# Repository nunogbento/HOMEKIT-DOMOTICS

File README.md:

# HOMEKIT-DOMOTICS

Personal collection of home-automation hardware and firmware around Apple HomeKit,
spanning multiple generations of boards and HomeKit integration techniques.

## Project layout

Each top-level folder is one project. Projects with a custom PCB have:

```
<Project>/
├── firmware/      one subfolder per firmware version (generation)
├── circuit/       PCB design files (.brd / .sch / .cam)
└── enclosure/     3D-printable bodies (where applicable)
```

Projects without a custom PCB omit `circuit/`, and use `enclosure/` only if a
3D-printed body exists.

## Active projects

### [PCCWDplus](PCCWDplus/) — custom PCB
Main panel board. Succession: MQTT (ESP8266) → HomeSpan (ESP32-C5).
Gen 2 (HAP/ESP8266) was attempted but failed; see archive notes.
- `firmware/Mqtt.MordomusESP8266/` — gen 1, MQTT/ESP8266 — **deployed**
- `firmware/HSPCCWDplus/` — gen 3, HomeSpan/ESP32-C5 — **WIP**, pin-compatible drop-in

### [MultiAccessory](MultiAccessory/) — custom PCB
Multi-device controller board. Gen 2 still deployed, gen 3 in progress.
- `firmware/HKMultiAccessory/` — gen 2, HAP/ESP8266 — **deployed**
- `firmware/HSPMultiAccessory/` — gen 3, HomeSpan/ESP32-C5 — **WIP**
- `firmware/HKSprinklerValve/` — gen 2 valve variant on the same board

### [ESP8266-ADC](ESP8266-ADC/) — custom PCB
Shared ESP8266-with-ADC board used for analog sensing applications.
- `firmware/HKSolarPanel/` — gen 2, HAP/ESP8266 — **deployed**, no successor planned
- `firmware/mqtt-SolarPanel/` — gen 1, archived firmware
- `firmware/Mqtt.ESP8266PlantComputer/` — gen 1, archived firmware

### [HSPCCWD](HSPCCWD/) — no custom hardware
HomeSpan reference implementation on a bare ESP32 devkit, serial-only.

### [ESP32Door](ESP32Door/) — no custom hardware
Door sensor using an off-the-shelf ESP32 module + 3D-printed enclosure.

### [Feeder](Feeder/) — no custom hardware, 3D-printed body
- `firmware/HKFEEDER/` — current
- `firmware/mqtt-RabitFeeder/` — earlier version

## HomeKit firmware generations

| Gen | Stack           | Chip         | Status                                |
|-----|-----------------|--------------|---------------------------------------|
| 1   | MQTT bridge     | ESP8266      | Mqtt.MordomusESP8266 still deployed   |
| 2   | Arduino-HomeKit | ESP8266      | HKMultiAccessory, HKSolarPanel still deployed; HKPCCWD archived (failed) |
| 3   | HomeSpan        | ESP32 / C5   | HSPCCWDplus, HSPMultiAccessory — WIP  |

Gen 2 failed on the PCCWD board because the ESP8266 could not handle HomeKit
at that board's accessory complexity. That's why the PCCWD lineage jumps
directly from gen 1 (MQTT) to gen 3 (HomeSpan).

## archive/

Everything superseded, retired, unfinished, unrelated, or not tied to an
active hardware project. Includes:
- `HKPCCWD/` (gen 2 failure)
- Early MQTT experiments (lightbulbs, rollerblinds, power meter, etc.)
- Side experiments (CameraWebServer, ESP-32CAM, SONOFFAPI, WaterDetector)
- `Tradfri-ICC-1/` — reverse-engineering research that informed MultiAccessory
- `MordomusAPI/`, `PowerMeter/`, `pccwdapi/`, `node-red-contrib-pccwd/` — no longer used
- `homebridge-host/` — Homebridge configuration, Node-RED flows, backups

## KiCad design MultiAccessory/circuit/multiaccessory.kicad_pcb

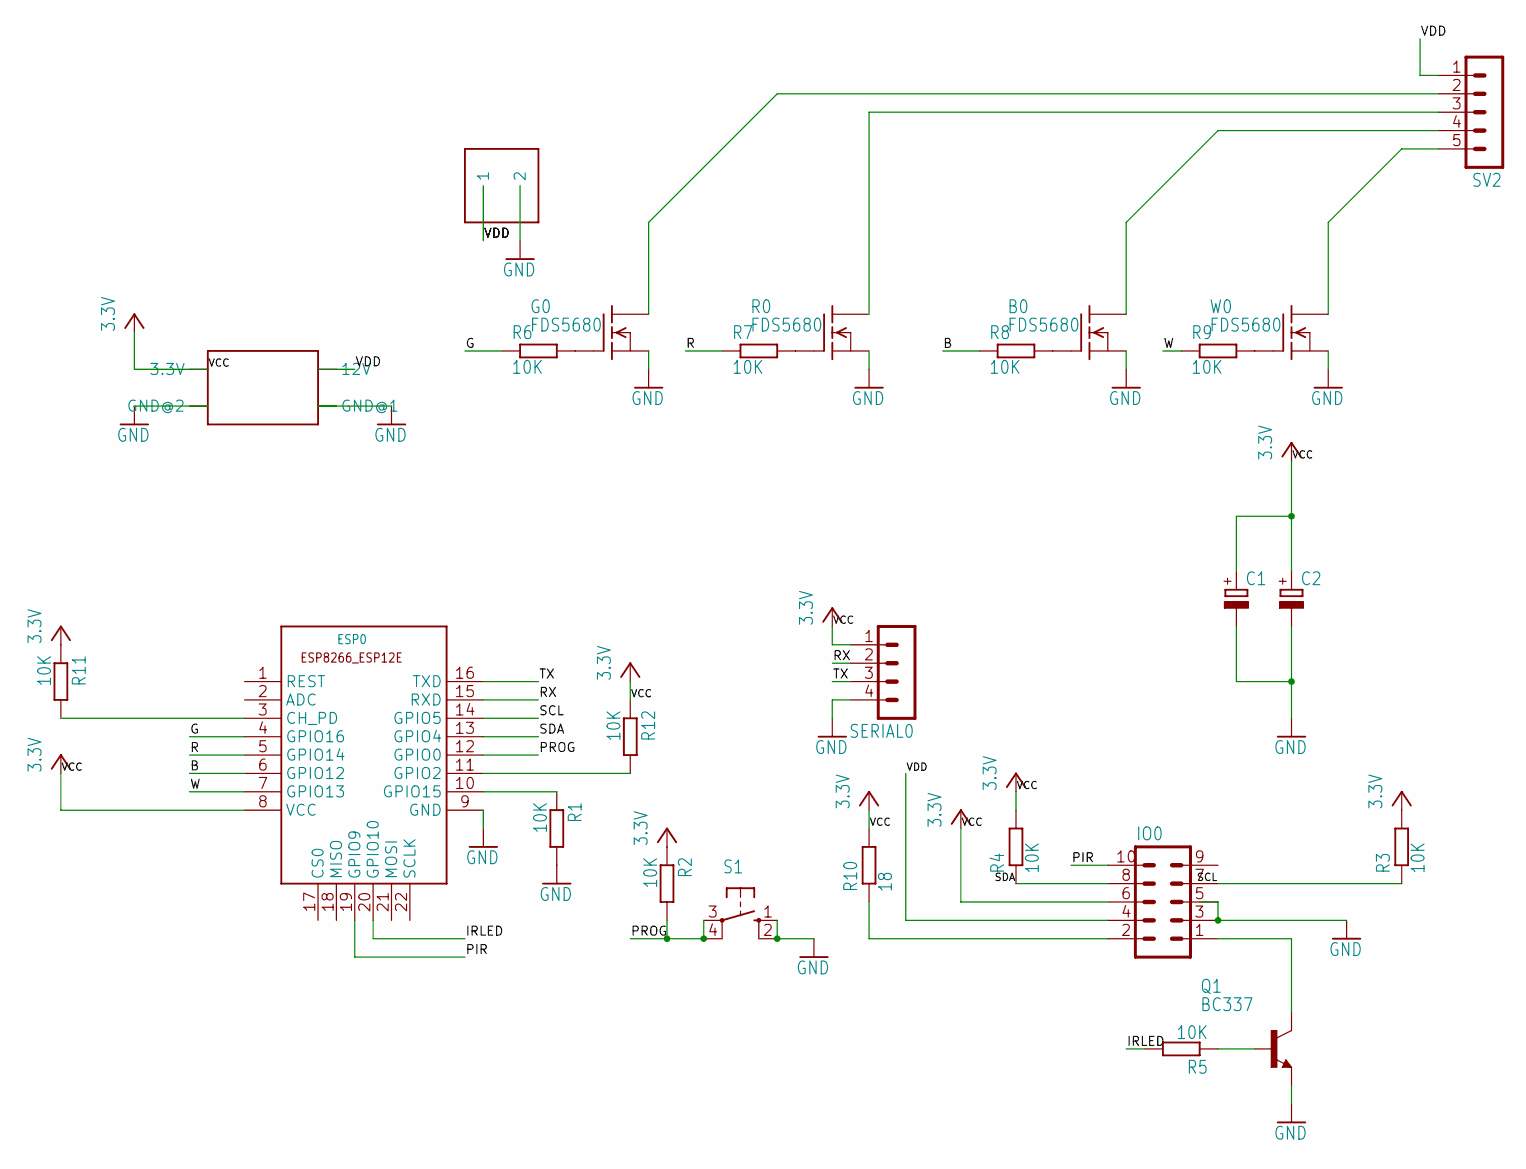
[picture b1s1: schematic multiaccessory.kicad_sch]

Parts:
B0: FDS5680; SO-8
C1, C2: CPOL-EUE2-5; E2-5
ESP0: ESP8266-12EESP8266-ESP12E; ESP8266-ESP12E
G0: FDS5680; SO-8
IO0: MA05-2
PWR1: MP2307-MINI-360
PWR_IN0: KF350-P2; KF350-2P
Q1: BC337; TO92
R0: FDS5680; SO-8
R1, R2, R3, R4, R5, R6, R7, R8, R9, R11, R12: 10K; R0603
R10: 18; R0603
S1: 10-XX; B3F-10XX
SERIAL0: MA04-1
SV2: MA05-1
W0: FDS5680; SO-8

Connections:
B: ESP0.6 (GPIO12), R8.1
DB: B0.5 (D), B0.6 (D), B0.7 (D), B0.8 (D), SV2.4
DG: G0.5 (D), G0.6 (D), G0.7 (D), G0.8 (D), SV2.2
DR: R0.5 (D), R0.6 (D), R0.7 (D), R0.8 (D), SV2.3
DW: SV2.5, W0.5 (D), W0.6 (D), W0.7 (D), W0.8 (D)
G: ESP0.4 (GPIO16), R6.1
GND: B0.1 (S), B0.2 (S), B0.3 (S), C1.-, C2.-, ESP0.9 (GND), G0.1 (S), G0.2 (S), G0.3 (S), IO0.3, IO0.5, PWR1.GND@1, PWR1.GND@2, PWR_IN0.2, Q1.1 (E), R0.1 (S), R0.2 (S), R0.3 (S), R1.2, S1.1 (S), S1.2 (S1), SERIAL0.4, W0.1 (S), W0.2 (S), W0.3 (S)
IRLED: ESP0.20 (GPIO10), R5.2
unnamed: ESP0.10 (GPIO15), R1.1
unnamed: ESP0.3 (CH_PD), R11.2
unnamed: ESP0.11 (GPIO2), R12.2
unnamed: G0.4 (G), R6.2
unnamed: Q1.2 (B), R5.1
unnamed: R0.4 (G), R7.2
unnamed: B0.4 (G), R8.2
unnamed: R9.2, W0.4 (G)
unnamed: IO0.2, R10.1
unnamed: IO0.1, Q1.3 (C)
PIR: ESP0.19 (GPIO9), IO0.10
PROG: ESP0.12 (GPIO0), R2.2, S1.3, S1.4 (P1)
R: ESP0.5 (GPIO14), R7.1
RX: ESP0.15 (RXD), SERIAL0.2
SCL: ESP0.14 (GPIO5), IO0.7, R3.1
SDA: ESP0.13 (GPIO4), IO0.8, R4.1
TX: ESP0.16 (TXD), SERIAL0.3
VCC: C1.+, C2.+, ESP0.8 (VCC), IO0.6, PWR1.3.3V, R2.1, R3.2, R4.2, R10.2, R11.1, R12.1, SERIAL0.1
VDD: IO0.4, PWR1.12V, PWR_IN0.1, SV2.1
W: ESP0.7 (GPIO13), R9.1

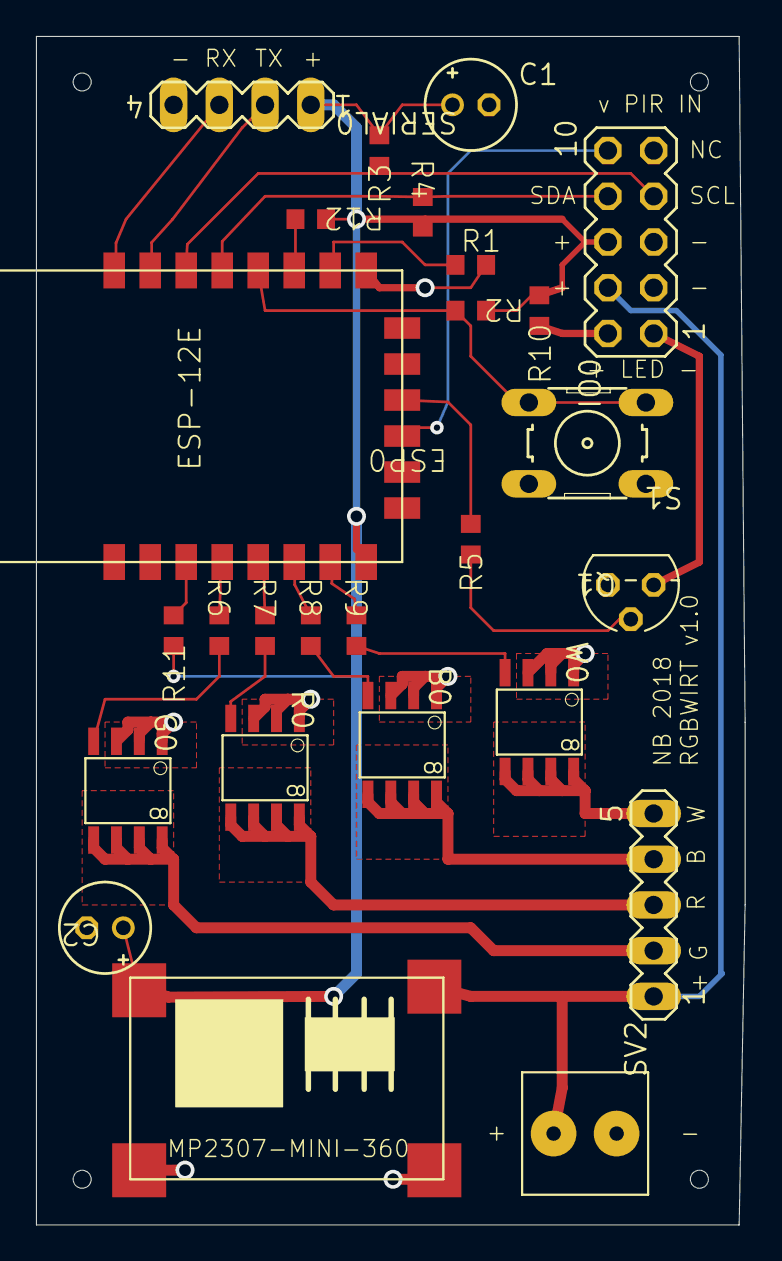
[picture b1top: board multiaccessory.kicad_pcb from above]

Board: 2 copper layers, 39.4 x 66.0 mm, 30 parts (0 on the bottom side), 28 nets.

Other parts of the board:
UNK_HOLE_0: dummyfp0
UNK_HOLE_1: dummyfp1
UNK_HOLE_2: dummyfp2
UNK_HOLE_3: dummyfp3

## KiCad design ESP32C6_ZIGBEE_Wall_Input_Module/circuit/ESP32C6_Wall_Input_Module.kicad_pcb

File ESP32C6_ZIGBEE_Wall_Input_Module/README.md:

# ESP32-C6 Zigbee In-Wall Input Module

A mains-powered, DIY alternative to the Philips Hue in-wall switch module.

It sits in the wall box behind your existing light switch, keeps the smart
bulbs **permanently powered**, and re-purposes the old mechanical switch as
two low-voltage inputs exposed over Zigbee. Because it runs off mains (not a
coin cell), it joins the mesh as a **Zigbee router**, strengthening the
network instead of being one more sleepy battery device.

## How it works

- A Hi-Link **HLK-PM01** (230 VAC → 5 V) feeds an **AMS1117-3.3**, powering a
  **WT0132C6-S5** (ESP32-C6 in the hand-solderable ESP-12F form factor).
- The lamp's live wire is bridged permanently on (joined with a Wago in the
  box) — the module never switches the load.
- The two existing switch contacts wire to two GPIO inputs (10 kΩ pull-up +
  RC filter each) and are published to Zigbee2MQTT as a **scene switch** —
  button *actions* (single / double / long, plus toggle/on/off), the same
  model as a Hue dimmer or a Modomus switch. HomeKit sees a **Stateless
  Programmable Switch**, not a door sensor.
- Each input's behaviour is **configurable from the Z2M profile** (see
  *Firmware behaviour* below), so the module works with a momentary push
  button *or* a bi-stable (rocker) toggle switch.

> ⚠️ **230 VAC.** Primary side is fused + MOV-protected and separated from the
> low-voltage side by a milled creepage slot (≥6 mm). The switch wires become
> SELV — disconnect them from mains before landing them. Needs a Neutral in
> the box (or install at the ceiling rose). See [HARDWARE.md](HARDWARE.md).

## Firmware behaviour

Each channel is a `genMultistateInput` endpoint reporting an **action**; a
`genMultistateOutput` on the same endpoint holds that channel's **mode**,
writable live from the Z2M UI and persisted in NVS.

| `mode_1` / `mode_2` | Emits | For |
|---|---|---|
| `momentary` *(default)* | `single` / `double` / `hold` | push buttons |
| `toggle` | `toggle` on every flip | rocker → HA does `light.toggle` |
| `toggle_directional` | `on` (closed) / `off` (open) | sync lamp to switch position |
| `toggle_scenes` | `single` / `double` from flip-count | multi-flip scenes off a rocker |

Actions arrive as `button_{1,2}_{single,double,hold,toggle,on,off}`.

**Diagnostics** (Z2M, diagnostic category):
- `device_temperature` — MCU die temp (health/overheat trend, not accurate
  ambient). **Polled** by the converter (a read every ~5 min), not reported:
  every Zigbee attribute-*report* path crashes this ESP-Zigbee build, so the
  firmware only refreshes the value and Z2M reads it. See the sketch header.
- `brownout_count` — increments on a brownout/unexpected reset, so a unit
  browning out in a wall reveals itself remotely with no serial cable.

**Zigbee OTA** — the module carries an OTA client, so after the first (wired)
flash every future update is wireless via Z2M's OTA override index, and images
are **rollback-guarded** (a bad boot reverts automatically). See
[ota/README.md](ota/README.md) for the full build → deploy → update process.

## Status

| Item | State |
|---|---|
| Schematic | ✅ Complete, ERC-clean (KiCad 10); WT0132C6-S5 symbol pinout corrected |
| PCB layout | ✅ Routed, DRC-clean — 45 × 36 mm, 2-layer (status LED on IO7 / pin 10) |
| Firmware | ✅ v8 (`0x01000007`) — scene-switch actions, per-channel modes, rollback-guarded OTA, polled temp + brownout telemetry |
| Z2M converter | ✅ External converter (actions + mode enums + diagnostics; temp polled) |
| Fabrication | 📦 Gerbers exported; **both boards hand-built, on mains, on v8, validated (buttons + modes + temp + brownout), ready to install** |
| OTA proven | ✅ Board 1 updated in-wall v3→v8 over the mesh (rollback-guarded) |

> **Regulator note:** use a *genuine* AMS1117-3.3. A counterfeit part that
> can't source the radio-TX surge causes brownouts on join (cool reg, low LQI,
> won't stay paired). Confirmed by bench-3.3 V bypass; fixed by a real part.
> See [HARDWARE.md](HARDWARE.md).

## Repository contents

| Path | What |
|---|---|
| [`ESP32C6_ZIGBEE_Wall_Input_Module.ino`](ESP32C6_ZIGBEE_Wall_Input_Module.ino) | Arduino sketch (compile-time board switch: WT0132C6-S5 or XIAO ESP32C6 prototype) |
| [`HARDWARE.md`](HARDWARE.md) | Circuit design, net-by-net description, BOM, install guide |
| [`ASSEMBLY.md`](ASSEMBLY.md) | Hand-assembly guide: part IDs/markings, build order, staged bring-up tests |
| [`FABRICATION.md`](FABRICATION.md) | JLCPCB order settings + gerber package |
| [`diy_esp32c6_2ch_input.js`](diy_esp32c6_2ch_input.js) | Zigbee2MQTT external converter (actions, per-channel mode enums, temp + brownout diagnostics, OTA) |
| [`ota/`](ota/) | Zigbee OTA: `make_ota.py` image builder, current `index.json` + `.ota` (mirrors the Pi's `ota_override/`), and [`ota/README.md`](ota/README.md) — the full update process |
| [`circuit/`](circuit/) | KiCad 10 project — schematic, board, custom WT0132C6-S5 library, gerbers (`fab/`) |
| [`docs/`](docs/) | Rendered board + schematic images |

## Board

| Top (mains side) | Bottom (logic side) |
|---|---|
|  |  |

The HLK-PM01 and screw terminals are on top; the WT0132C6-S5 is on the bottom
with its antenna overhanging the board edge. The notch in the ground pour and
the milled slot keep the 230 V primary isolated from the SELV side.

## Prototype / bring-up bench

The bring-up rig: WT0132C6-S5 board (blue status LED lit) fed from the
HLK-PM01, a USB-UART for the first flash, test-clip leads to the two inputs,
and a real dual **rocker** wall switch on the bench — the setup used to
validate the toggle-switch modes and the genuine-AMS1117 fix.

## Firmware build

Arduino IDE with the ESP32 core (Zigbee ZCZR mode + partition). Pick the board
at the top of the sketch:

```c
//#define BOARD_XIAO_ESP32C6    // breadboard prototype
#define BOARD_WT0132C6_S5       // final mains board
```

First flash is over UART (hold IO9 low, pulse EN); **after that, update over
the air** via Z2M OTA — no wires. Hold the BOOT button 5 s to factory reset /
re-pair. Status LED (IO7, active-low) blinks while joining, solid ~3 s when
connected, then off (it lives in a wall).

## Schematic

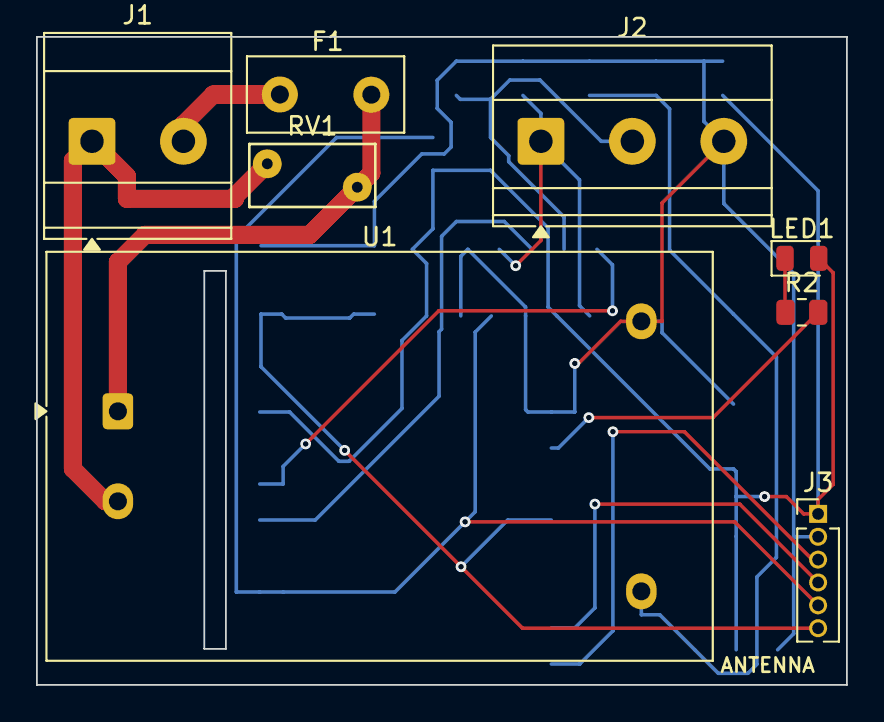
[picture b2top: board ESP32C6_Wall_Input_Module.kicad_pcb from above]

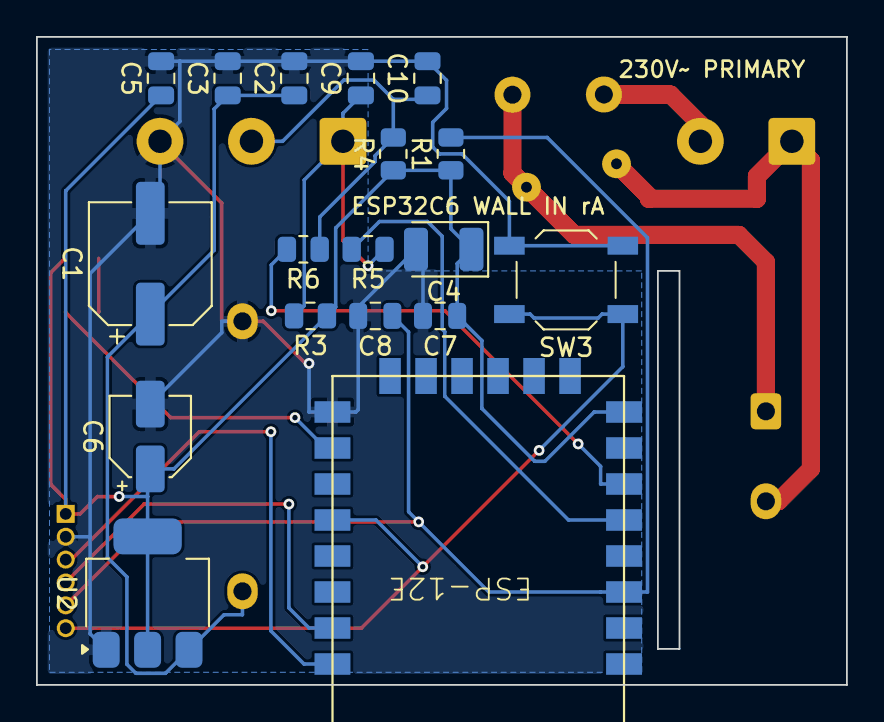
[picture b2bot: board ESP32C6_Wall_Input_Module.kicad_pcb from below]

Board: 2 copper layers, 45.0 x 36.0 mm, 26 parts (18 on the bottom side), 16 nets.

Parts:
C1: 100u; CP_Elec_6.3x5.4
C2, C5, C7, C9, C10: 100n; C_0805_2012Metric
C3: 10u; C_0805_2012Metric
C4: 22u; CP_EIA-3528-21_Kemet-B
C6: 47u; CP_Elec_4x5.4
C8: 1u; C_0805_2012Metric
F1: 500mA T; Fuse_Littelfuse_395Series
J1: MAINS IN; TerminalBlock_Phoenix_MKDS-3-2-5.08_1x02_P5.08mm_Horizontal
J2: WALL SWITCHES; TerminalBlock_Phoenix_MKDS-1,5-3-5.08_1x03_P5.08mm_Horizont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
J3: PROG; PinHeader_1x06_P1.27mm_Vertical
LED1: STATUS; LED_0805_2012Metric
R1, R3, R4: 10k; R_0805_2012Metric
R2, R5, R6: 1k; R_0805_2012Metric
RV1: 275VAC; RV_Disc_D7mm_W3.5mm_P5mm
SW3: BOOT; SW_SPST_TL3342
U1: HLK-PM01; Converter_ACDC_Hi-Link_HLK-PMxx
U2: AMS1117-3.3; SOT-223-3_TabPin2
U3: WT0132C6-S5

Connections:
+3V3: C4.1, C5.1, C6.1, C7.1, J3.1, LED1.2 (A), R1.1, R3.1, R4.1, U2.2 (VO), U3.8 (VCC)
+5V: C1.1, C2.1, C3.1, U1.4 (+Vout), U2.3 (VI)
/EN: C8.1, J3.5, R1.2, U3.3 (EN)
/IO9: J3.6, SW3.1, U3.12 (IO9)
/L: F1.1, J1.2
/N: J1.1, RV1.2, U1.2 (AC/N)
/RXD0: J3.4, U3.15 (RXD)
/STATUS_LED: R2.2, U3.10 (IO7)
/SW1: C9.1, J2.1, R3.2, R5.1
/SW1_IN: R5.2, U3.5 (IO4/MTMS)
/SW2: C10.1, J2.2, R4.2, R6.1
/SW2_IN: R6.2, U3.6 (IO5/MTDI)
/TXD0: J3.3, U3.16 (TXD)
GND: C1.2, C2.2, C3.2, C4.2, C5.2, C6.2, C7.2, C8.2, C9.2, C10.2, J2.3, J3.2, SW3.2, U1.3 (-Vout), U2.1 (GND), U3.9 (GND)
unnamed: LED1.1 (K), R2.1
unnamed: F1.2, RV1.1, U1.1 (AC/L)

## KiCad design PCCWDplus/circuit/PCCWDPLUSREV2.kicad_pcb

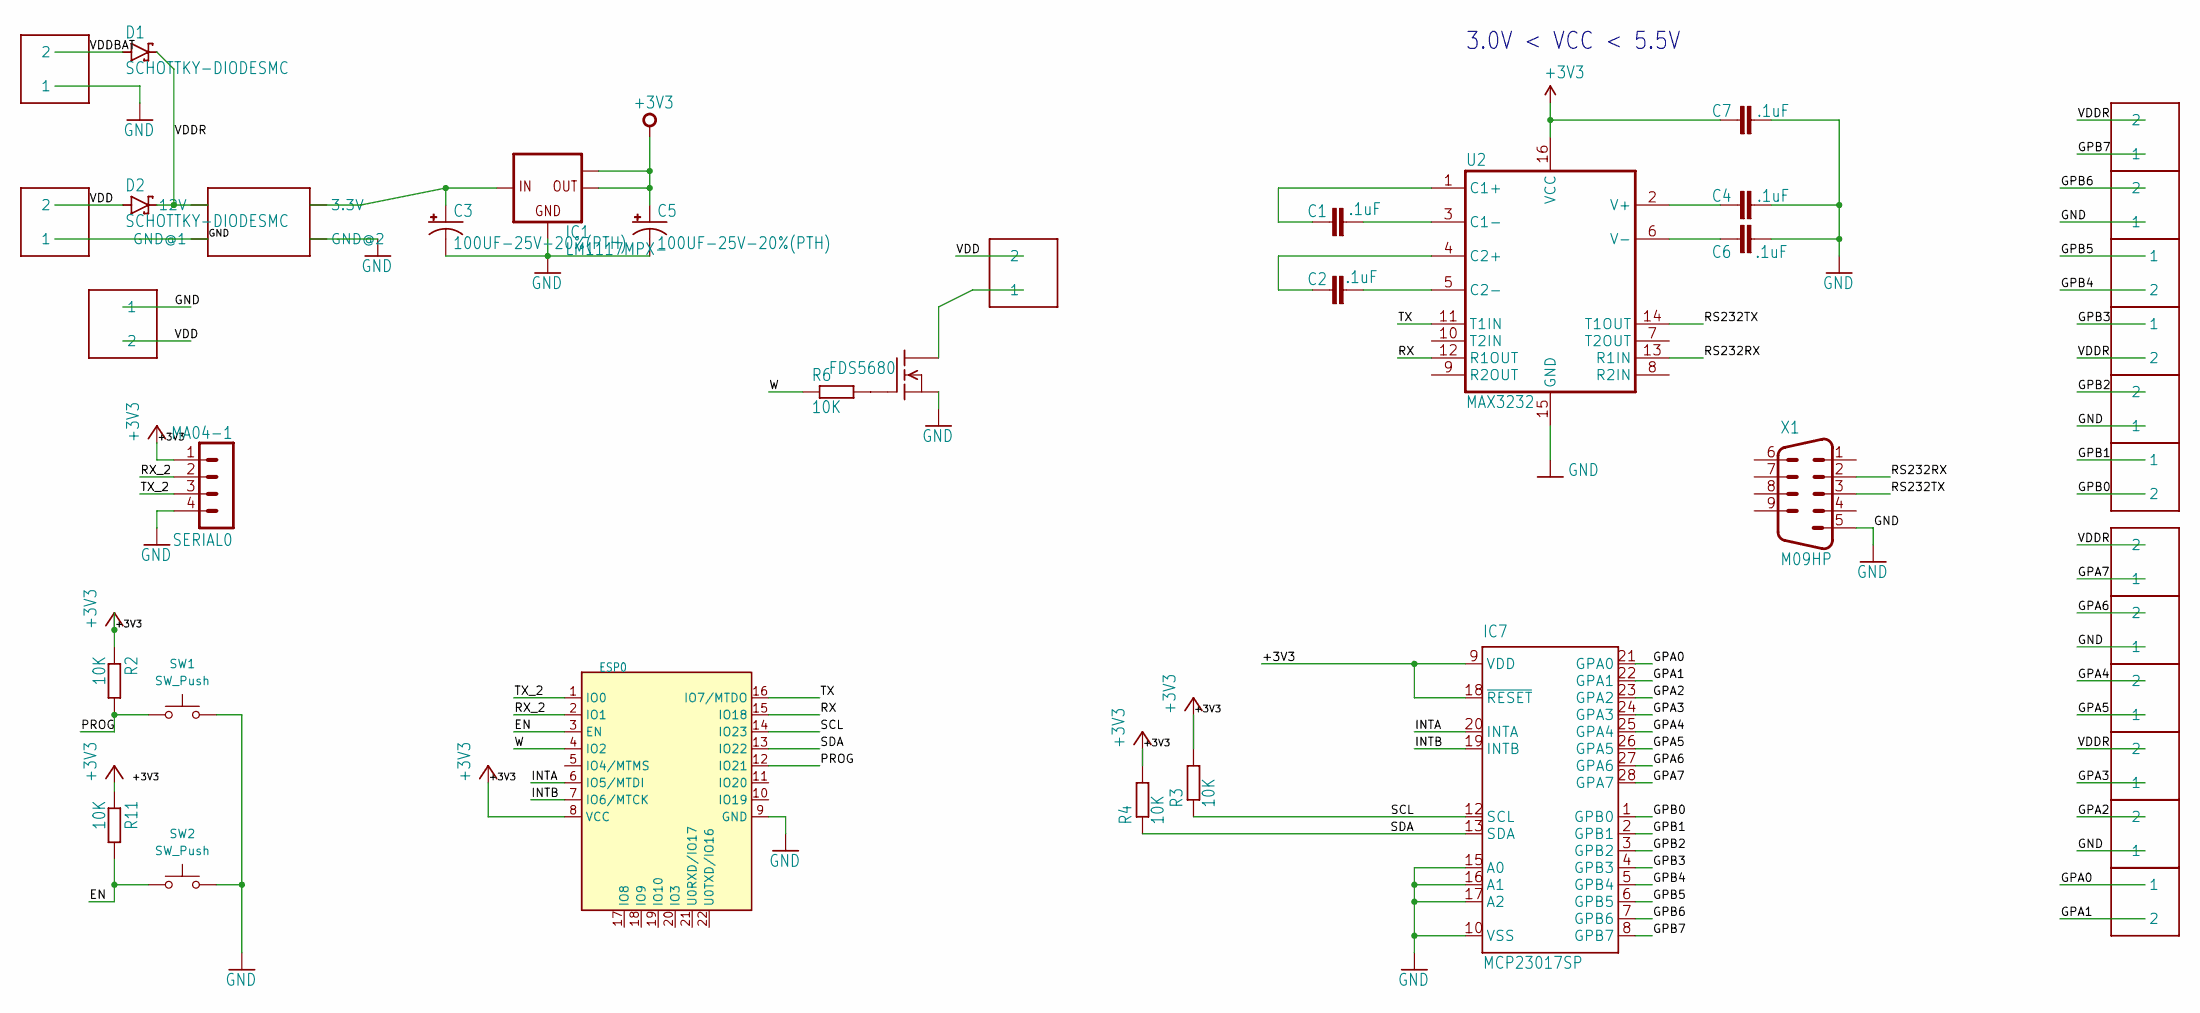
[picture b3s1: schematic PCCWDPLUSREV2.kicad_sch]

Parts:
C1, C2, C4, C6, C7: .1uF; 0603-CAP
C3, C5: 100UF-25V-20%(PTH); CPOL-RADIAL-100UF-25V
D1, D2: SCHOTTKY-DIODESMC; SMC
ESP0: WT0132C6-S5; ESP-12F
G0: FDS5680; SO-8
IC1: LM1117MPX-; SOT223
IC7: MCP23017SP; DIL28-3
PWR1: MP2307-MINI-360
PWR_IN0, PWR_IN1, PWR_IN2, PWR_IN3, PWR_IN4, PWR_IN5, PWR_IN6, PWR_IN7, PWR_IN8, PWR_IN9, PWR_IN10, PWR_IN11, PWR_IN12, PWR_IN13, PWR_IN14: KF350-P2; KF350-2P
PWR_INBAT0: KF350-P2; KF350-2P
R2, R3, R4, R6, R11: 10K; R0603
SERIAL0: MA04-1
SW1, SW2: SW_Push; SW_TH_Tactile_Omron_B3F-100x
U2: MAX3232; SO016
X1: M09HP

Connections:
+3V3: C5.1 (+), C7.1, ESP0.8 (VCC), IC1.2 (OUT), IC1.TAB (OUT1), IC7.9 (VDD), IC7.18 (~RESET), R2.1, R3.2, R4.2, R11.1, SERIAL0.1, U2.16 (VCC)
/GPA0: IC7.21 (GPA0), PWR_IN11.1
/GPA1: IC7.22 (GPA1), PWR_IN11.2
/GPA2: IC7.23 (GPA2), PWR_IN12.2
/GPA3: IC7.24 (GPA3), PWR_IN13.1
/GPA4: IC7.25 (GPA4), PWR_IN3.2
/GPA5: IC7.26 (GPA5), PWR_IN3.1
/GPA6: IC7.27 (GPA6), PWR_IN2.2
/GPA7: IC7.28 (GPA7), PWR_IN10.1
/GPB0: IC7.1 (GPB0), PWR_IN6.2
/GPB1: IC7.2 (GPB1), PWR_IN6.1
/GPB2: IC7.3 (GPB2), PWR_IN5.2
/GPB3: IC7.4 (GPB3), PWR_IN7.1
/GPB4: IC7.5 (GPB4), PWR_IN9.2
/GPB5: IC7.6 (GPB5), PWR_IN9.1
/GPB6: IC7.7 (GPB6), PWR_IN8.2
/GPB7: IC7.8 (GPB7), PWR_IN4.1
/INTA: ESP0.6 (IO5/MTDI), IC7.20 (INTA)
/INTB: ESP0.7 (IO6/MTCK), IC7.19 (INTB)
/PROG: ESP0.12 (IO21), R2.2, SW1.1; also elsewhere on the board
/RS232RX: U2.13 (R1IN), X1.2
/RS232TX: U2.14 (T1OUT), X1.3
/RX: ESP0.15 (IO18), U2.12 (R1OUT)
/RX_2: ESP0.2 (IO1), SERIAL0.2
/SCL: ESP0.14 (IO23), IC7.12 (SCL), R3.1
/SDA: ESP0.13 (IO22), IC7.13 (SDA), R4.1
/TX: ESP0.16 (IO7/MTDO), U2.11 (T1IN)
/TX_2: ESP0.1 (IO0), SERIAL0.3
/VDD: D2.A, PWR_IN0.2, PWR_IN1.2, PWR_IN14.2
/VDDBAT: D1.A, PWR_INBAT0.2
/VDDR: D1.C, D2.C, PWR1.12V, PWR_IN4.2, PWR_IN7.2, PWR_IN10.2, PWR_IN13.2
/W: ESP0.4 (IO2), R6.1
GND: C3.2 (-), C4.2, C5.2 (-), C6.2, C7.2, ESP0.9 (GND), G0.1 (S), G0.2 (S), G0.3 (S), IC1.1 (GND), IC7.10 (VSS), IC7.15 (A0), IC7.16 (A1), IC7.17 (A2), PWR1.GND@1, PWR1.GND@2, PWR_IN0.1, PWR_IN2.1, PWR_IN5.1, PWR_IN8.1, PWR_IN12.1, PWR_IN14.1, PWR_INBAT0.1, SERIAL0.4, SW1.2, SW2.2, U2.15 (GND), X1.5; also elsewhere on the board
unnamed: C3.1 (+), IC1.3 (IN), PWR1.3.3V
unnamed: ESP0.3 (EN), R11.2, SW2.1
unnamed: G0.5 (D), G0.6 (D), G0.7 (D), G0.8 (D), PWR_IN1.1
unnamed: G0.4 (G), R6.2
unnamed: C1.1, U2.1 (C1+)
unnamed: C1.2, U2.3 (C1-)
unnamed: C2.1, U2.4 (C2+)
unnamed: C2.2, U2.5 (C2-)
unnamed: C4.1, U2.2 (V+)
unnamed: C6.1, U2.6 (V-)

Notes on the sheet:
3.0V < VCC < 5.5V

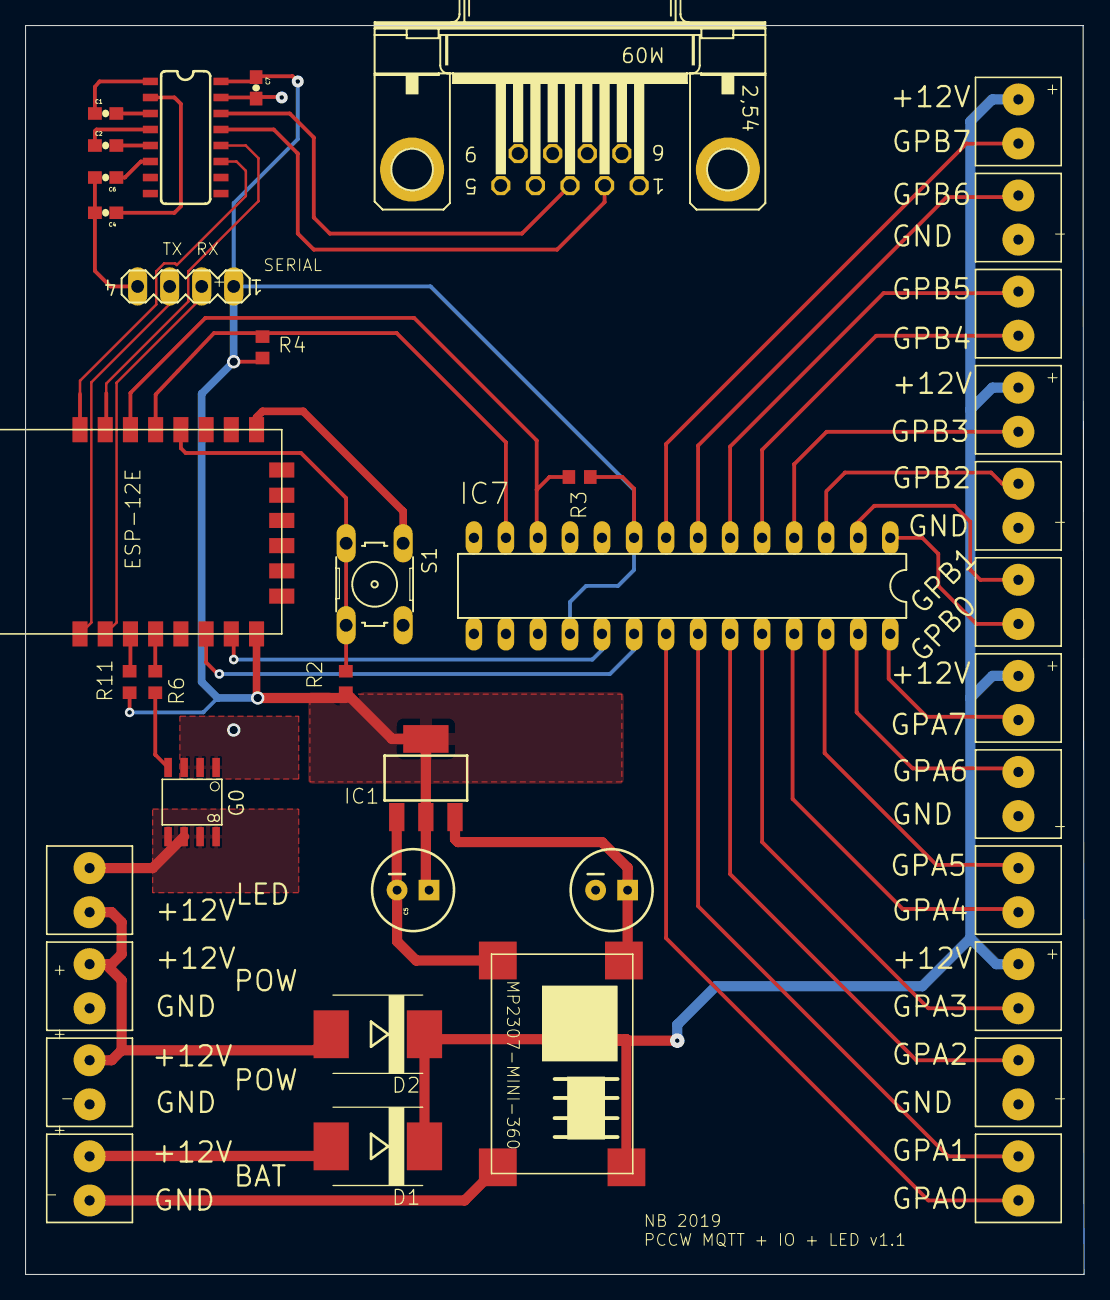
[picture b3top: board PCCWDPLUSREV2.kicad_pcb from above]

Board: 2 copper layers, 83.9 x 99.1 mm, 39 parts (0 on the bottom side), 43 nets.

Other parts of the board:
S1: 10-XX; B3F-10XX_377

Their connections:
/PROG: S1.3, S1.4 (P1); also elsewhere on the board
GND: S1.1 (S), S1.2 (S1); also elsewhere on the board

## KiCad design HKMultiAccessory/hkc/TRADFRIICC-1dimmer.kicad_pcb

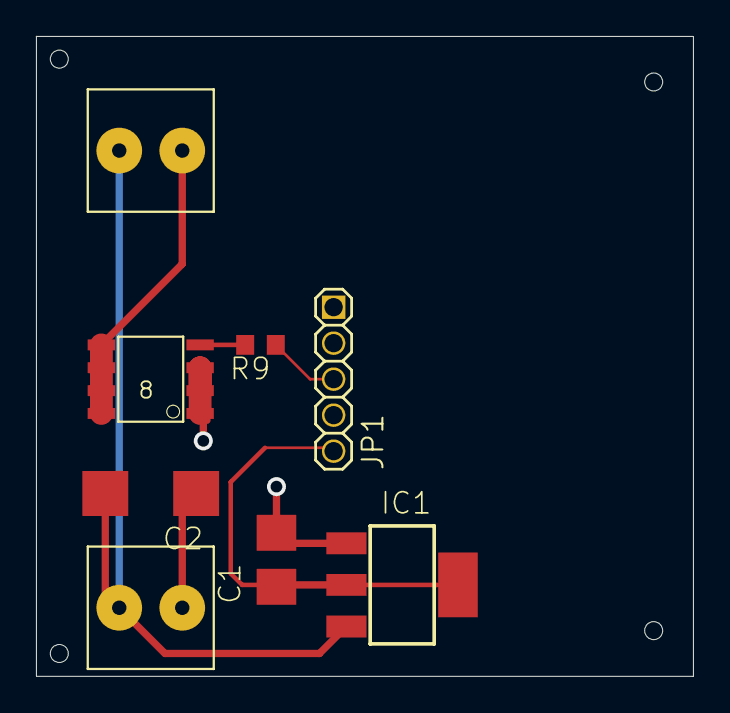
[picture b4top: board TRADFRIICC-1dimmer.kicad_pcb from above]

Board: 2 copper layers, 36.5 x 35.5 mm, 12 parts (0 on the bottom side), 6 nets.

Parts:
@HOLE0, @HOLE1, @HOLE2, @HOLE3: (no value)
C1: 100u; CT3528_334
C2: 10u; C_6032-28R_334
IC1: LM1117MPX-3.3; SOT223
JP1: 1_05X2MM_325
PWR_IN0, PWR_IN1: KF350-P2; KF350-2P
R9: 10K; R0603
W0: SO-8

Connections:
+3V3: C1.+, IC1.2, IC1.TAB, JP1.5
DW: PWR_IN1.1, W0.5, W0.6, W0.7, W0.8
GND: C1.-, C2.-, IC1.1, JP1.4, PWR_IN0.1, W0.1, W0.2, W0.3
unnamed: R9.2, W0.4
PWM: JP1.3, R9.1
VDD: C2.+, IC1.3, PWR_IN0.2, PWR_IN1.2

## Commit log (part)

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2017-01-22 working
2017-01-22 fixes
2018-01-08 no message
2018-01-09 Wifi Manager
2018-01-09 cleanup
2018-01-13 temp & humidity sensor added, hardware ok
2018-01-14 motion sensor
2018-04-23 rabbit feeder
2018-04-30 PCCWD API with Initialization, power loss resilience. Mordomus Lights moved to mqtt plugin
2018-05-02 PCCWD mqtt set + nodered flows update
2018-06-04 fix config + IR implented
2018-07-02 added
2019-06-25 woking pccwd io
2019-08-12 working pccwd API
2019-08-12 settings prj
2019-11-05 stuff
2019-11-05 Copy for PCB Order
2020-04-08 Working Plan Computer + Box
2020-05-15 fixed crash
2020-05-16 less verbose log
2021-03-18 valvetype
2021-05-14 testing begins
2021-05-14 basic on/of OK dimmer OK fixes
2021-05-14 LED dual and dual dimmer OK
2021-05-14 LEDController ok only hsi2RGB not that good
2021-05-14 temperature sensor ok
2021-05-14 AC compiling
2021-05-14 ac pregress but not good yet
2021-05-15 OTA Good, AC not crashing but still acting up.
2021-05-17 deployed
2021-05-17 AC ALL Good now
2021-05-18 hksolarpanel added
2021-05-18 hksp compiling
2021-05-18 changed ac
2021-05-21 fixes on AC controller
2021-05-29 hkpccwd
2021-06-04 New Hmespan Based ESP32 PCCWD controller working
2022-01-20 added temp log via mqtt + fixes
2023-03-21 Sofware hanges
2023-03-21 Board updates
2024-05-15 HK irrigation valves
2024-05-15 Bridge Version
2024-05-16 back to single accessory. valve 4 fixed.
2024-05-17 hksprinkler loop and calbacks done
2024-09-06 PCCWD updated dependencies
2024-09-06 Improved Homebridge sync
2024-09-06 Update PCCWDAPo.ino
    Added NO Motion Sensor support
2024-09-10 bug fixing
2024-10-13 minor stuff
2025-06-16 Created hsp muliaccessory for esp32c6
2025-06-16 merge
2025-06-17 Implementation of hspmultiaccessory
2025-06-17 ac reviwwd
2025-06-20 working almost
2025-06-21 AC making sense now
2025-06-22 tunning
2025-06-23 alternative mode AC test
2025-06-23 refining hspmultiaccessory
2025-06-24 DONE HSP multiaccessory
2025-06-24 hspmultiaccessory final
2026-04-17 move
2026-06-18 Doorbel phase 1
2026-06-18 moving
